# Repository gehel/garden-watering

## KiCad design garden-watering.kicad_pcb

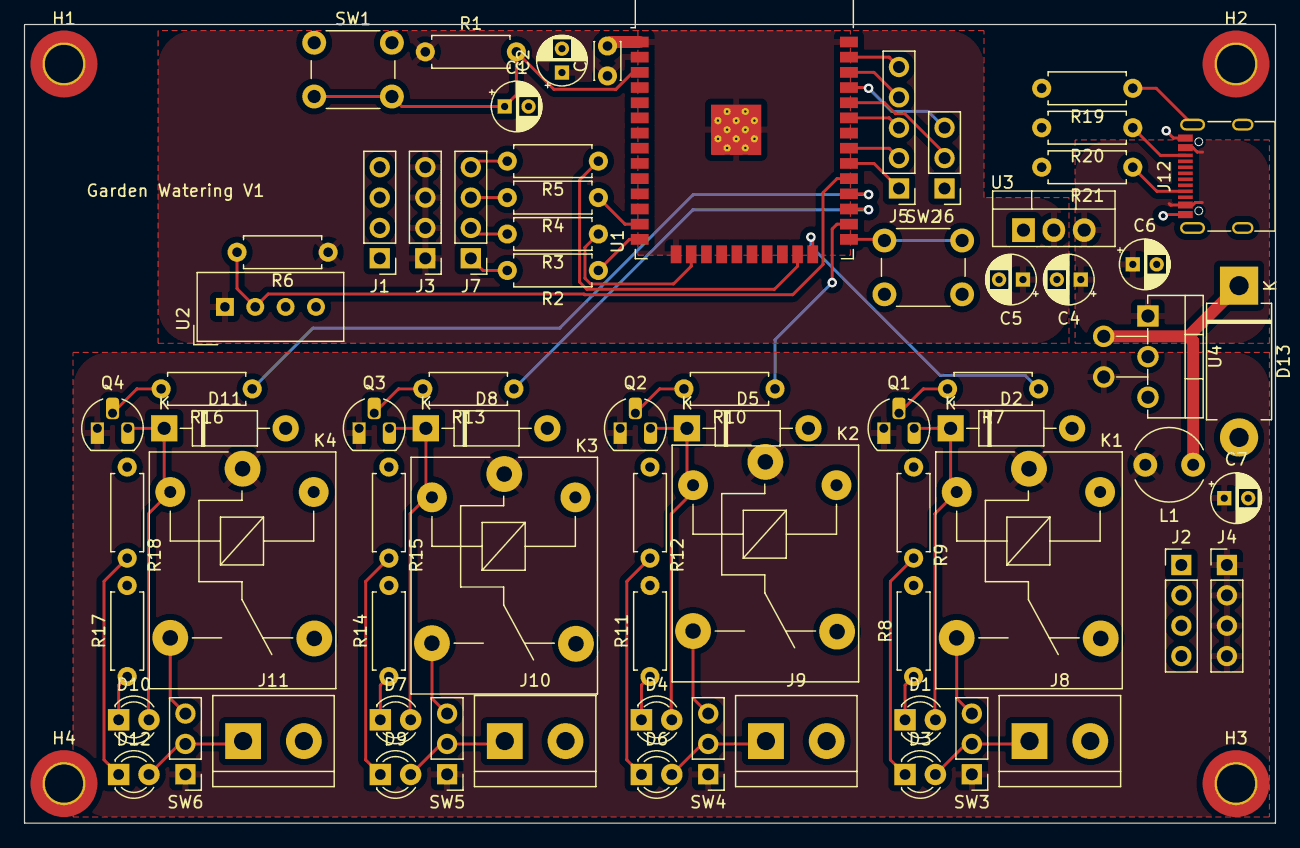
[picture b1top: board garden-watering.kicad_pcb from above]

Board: 2 copper layers, 104.6 x 66.8 mm, 76 parts (0 on the bottom side), 56 nets.

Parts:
C1: 1uF; CP_Radial_D4.0mm_P2.00mm
C2, C4: 10uF; CP_Radial_D4.0mm_P2.00mm
C3: 100nF; C_Disc_D3.0mm_W2.0mm_P2.50mm
C5, C6: 100uF; CP_Radial_D4.0mm_P2.00mm
C7: 220uF; CP_Radial_D4.0mm_P2.00mm
D1, D3, D4, D6, D7, D9, D10, D12: LED; LED_D3.0mm
D2, D5, D8, D11: 1N4007; D_DO-41_SOD81_P10.16mm_Horizontal
D13: D_Schottky; D_DO-201AD_P12.70mm_Horizontal
H1, H2, H3, H4: MountingHole_Pad; MountingHole_3.2mm_M3_DIN965_Pad_TopBottom
J1, J2: GND; PinHeader_1x04_P2.54mm_Vertical
J3: +3.3V; PinHeader_1x04_P2.54mm_Vertical
J4: +12V; PinHeader_1x04_P2.54mm_Vertical
J5: GPIO; PinHeader_1x05_P2.54mm_Vertical
J6: UART; PinHeader_1x03_P2.54mm_Vertical
J7: JTAG; PinHeader_1x04_P2.54mm_Vertical
J8, J9, J10, J11: Screw_Terminal_01x02; TerminalBlock_bornier-2_P5.08mm
J12: USB_C_Receptacle; USB_C_Receptacle_G-Switch_GT-USB-7010ASV
K1, K2, K3, K4: SANYOU_SRD_Form_C; Relay_SPDT_SANYOU_SRD_Series_Form_C
L1: 330uH; L_Radial_D6.0mm_P4.00mm
Q1, Q2, Q3, Q4: 2N2222; TO-92L_HandSolder
R1, R6: 10K; R_Axial_DIN0207_L6.3mm_D2.5mm_P7.62mm_Horizontal
R2, R3, R4, R5: 100R; R_Axial_DIN0207_L6.3mm_D2.5mm_P7.62mm_Horizontal
R7, R10, R13, R16: 1K; R_Axial_DIN0207_L6.3mm_D2.5mm_P7.62mm_Horizontal
R8, R9, R11, R12, R14, R15, R17, R18: 220R; R_Axial_DIN0207_L6.3mm_D2.5mm_P7.62mm_Horizontal
R19: 1M; R_Axial_DIN0207_L6.3mm_D2.5mm_P7.62mm_Horizontal
R20, R21: 5.11K; R_Axial_DIN0207_L6.3mm_D2.5mm_P7.62mm_Horizontal
SW1: RESET; SW_PUSH_6mm
SW2: PROG; SW_PUSH_6mm
SW3, SW4, SW5, SW6: SW_SPDT; PinHeader_1x03_P2.54mm_Vertical
U1: ESP32-WROOM-32
U2: DHT11; Aosong_DHT11_5.5x12.0_P2.54mm
U3: LM1117T-3.3; TO-220-3_Vertical
U4: LM2576T-12; TO-220-5_P3.4x3.7mm_StaggerEven_Lead3.8mm_Vertical

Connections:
+3.3V: C2.1, C3.1, C5.1, J3.1, J3.2, J3.3, J3.4, R1.1, R6.1, U1.2 (VDD), U2.1 (VCC), U3.2 (VO)
+12V: C7.1, J4.1, J4.2, J4.3, J4.4, K1.1, K2.1, K3.1, K4.1, L1.2, Q1.1 (C), Q2.1 (C), Q3.1 (C), Q4.1 (C), SW3.1 (A), SW4.1 (A), SW5.1 (A), SW6.1 (A), U4.4 (FB)
/USB-Power/D+: J12.A6 (D+), J12.B6 (D+)
/USB-Power/D-: J12.A7 (D-), J12.B7 (D-)
DHT: R6.2, U1.29 (IO5), U2.2 (IO)
GND: C1.2, C2.2, C3.2, C4.2, C5.2, C6.2, C7.2, D2.2 (A), D5.2 (A), D8.2 (A), D11.2 (A), D13.2 (A), H1.1, H2.1, H3.1, H4.1, J1.1, J1.2, J1.3, J1.4, J2.1, J2.2, J2.3, J2.4, J6.1, J8.2, J9.2, J10.2, J11.2, J12.A1 (GND), J12.A12 (GND), J12.B1 (GND), J12.B12 (GND), K1.5, K2.5, K3.5, K4.5, R8.2, R9.2, R11.2, R12.2, R14.2, R15.2, R17.2, R18.2, R19.2, R20.2, R21.2, SW1.1, SW2.2, U1.1 (GND), U1.15 (GND), U1.38 (GND), U1.39 (GND), U2.4 (GND), U3.1 (GND), U4.3 (GND), U4.5 (~ON/OFF)
IO18: J5.1, U1.30 (IO18)
IO19: J5.2, U1.31 (IO19)
IO21: J5.3, U1.33 (IO21)
IO22: J5.4, U1.36 (IO22)
IO23: J5.5, U1.37 (IO23)
MTCK: R3.1, U1.16 (IO13)
MTDI: R2.1, U1.14 (IO12)
MTDO: R5.1, U1.23 (IO15)
MTMS: R4.1, U1.13 (IO14)
unnamed: D1.2 (A), D2.1 (K), K1.2, Q1.3 (E)
unnamed: D1.1 (K), R8.1
unnamed: D3.2 (A), J8.1, SW3.2 (B)
unnamed: D3.1 (K), R9.1
unnamed: D4.2 (A), D5.1 (K), K2.2, Q2.3 (E)
unnamed: D4.1 (K), R11.1
unnamed: D6.2 (A), J9.1, SW4.2 (B)
unnamed: D6.1 (K), R12.1
unnamed: D7.2 (A), D8.1 (K), K3.2, Q3.3 (E)
unnamed: D7.1 (K), R14.1
unnamed: D9.2 (A), J10.1, SW5.2 (B)
unnamed: D9.1 (K), R15.1
unnamed: D10.2 (A), D11.1 (K), K4.2, Q4.3 (E)
unnamed: D10.1 (K), R17.1
unnamed: D12.2 (A), J11.1, SW6.2 (B)
unnamed: D12.1 (K), R18.1
unnamed: D13.1 (K), L1.1, U4.2 (OUT)
unnamed: J7.1, R2.2
unnamed: J7.2, R3.2
unnamed: J7.3, R4.2
unnamed: J7.4, R5.2
unnamed: J12.A5 (CC1), R21.1
unnamed: J12.B5 (CC2), R20.1
unnamed: J12.S1 (SHIELD), R19.1
unnamed: Q1.2 (B), R7.2
unnamed: Q2.2 (B), R10.2
unnamed: Q3.2 (B), R13.2
unnamed: Q4.2 (B), R16.2
unnamed: K1.3, SW3.3 (C)
unnamed: K2.3, SW4.3 (C)
unnamed: K3.3, SW5.3 (C)
unnamed: K4.3, SW6.3 (C)
unnamed: C1.1, R1.2, SW1.2, U1.3 (EN)
unnamed: SW2.1, U1.25 (IO0)
RELAY_1: R7.1, U1.24 (IO2)
RELAY_2: R10.1, U1.26 (IO4)
RELAY_3: R13.1, U1.27 (IO16)
RELAY_4: R16.1, U1.28 (IO17)
RX: J6.2, U1.34 (RXD0/IO3)
TX: J6.3, U1.35 (TXD0/IO1)
VBUS: C4.1, C6.1, J12.A4 (VBUS), J12.A9 (VBUS), J12.B4 (VBUS), J12.B9 (VBUS), U3.3 (VI), U4.1 (VIN)

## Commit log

2023-10-18 misc
2023-10-20 gerber params
2023-11-13 better footprint for hand soldering
